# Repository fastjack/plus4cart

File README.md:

# plus4cart
This is an even more modernized (SMD-only) version of the C264Cart.

I removed the through-hole jumpers and other through-hole components and replaced them with SMD versions. Only the (E)EPROM remains as a trough-hole component.

The dimensions of the PCB remain unchanged and it should still fit into the [original looking cartridge case](https://www.thingiverse.com/thing:3657002).

Original README below

# C264Cart

The C264Cart ist a modernized ROM cartridge for the Commodore 264 family of 8-bit computers, the Commodore C16, C116, and Plus/4.

I started out by first reverse engineering and replicating the layout of an original ROM cartridge. Then I adapted it to better suit EPROMS and EEPROMS that are still readily  available today, such as the W27C512 and W27C020.  The layout was also scaled down to save shipping costs, but still fits the original cartridge shells.

See my [blog post](https://www.hackup.net/2023/12/making-cartridges-for-the-commodore-c16-c116-and-plus-4/) for more details.

I also created a simplified version of the original cartridge case for 3D printing that works well with the C264Cart. It is currently available for personal use on [Thingiverse](https://www.thingiverse.com/thing:6309306) and [Printables](https://www.printables.com/model/644139-commodore-264-cartridge-case-redux-for-c16-and-plu).

## Configuration Options

There are two things that need to be configured, the type of EPROM to be used and the size of the targeted ROM images. 

The C264Cart can be configured to support either 16k ROM images or 32k ROM images by setting JP6 and JP7 accordingly. 32k ROM images for the 264 computers usually consist of two 16k parts that were originally stored in two separate ROMs. On the C264Cart in 32k mode, both parts go into the same EPROM with the upper part directly following the lower one. As a result, A14 cannot be used for external bank switching in 32k mode. It is automatically selected by the cartridge.

If the C264Cart is configured for 16k mode R1, D1, and D2 don't need to be populated. These components are used in 32k mode, only.

The C264Cart supports 27C512, 27C020, and 27C040 (E)EPROMs. Make sure that these ICs are always aligned to the top of the cartridge as indicated on the silkscreen and that the jumpers JP4 and JP5 are set correctly!

### 27C512 for 4 ROM images with 16k each

| Address   |             | A14 | A15 |
|----------:|-------------|:---:|:---:|
| 0x0000    | ROM 1       |  0  |  0  |
| 0x4000    | ROM 2       |  1  |  0  |
| 0x8000    | ROM 3       |  0  |  1  |
| 0xC000    | ROM 4       |  1  |  1  |

### 27C020 for 16 ROM images with 16k each

| Address    |             | A14 | A15 | A16 | A17 |
|-----------:|-------------|:---:|:---:|:---:|:---:|
| 0x00000    | ROM 1       |  0  |  0  |  0  |  0  |
| 0x04000    | ROM 2       |  1  |  0  |  0  |  0  |
| 0x08000    | ROM 3       |  0  |  1  |  0  |  0  |
| 0x0C000    | ROM 4       |  1  |  1  |  0  |  0  |
| 0x10000    | ROM 5       |  0  |  0  |  1  |  0  |
| ...        | ...         | ... | ... | ... | ... |
| 0x3C000    | ROM 16      |  1  |  1  |  1  |  1  |

### 27C040 for 32 ROM images with 16k each

| Address    |             | A14 | A15 | A16 | A17 | A18 |
|-----------:|-------------|:---:|:---:|:---:|:---:|:---:|
| 0x00000    | ROM 1       |  0  |  0  |  0  |  0  |  0  |
| 0x04000    | ROM 2       |  1  |  0  |  0  |  0  |  0  |
| 0x08000    | ROM 3       |  0  |  1  |  0  |  0  |  0  |
| 0x0C000    | ROM 4       |  1  |  1  |  0  |  0  |  0  |
| 0x10000    | ROM 5       |  0  |  0  |  1  |  0  |  0  |
| ...        | ...         | ... | ... | ... | ... | ... |
| 0x7C000    | ROM 32      |  1  |  1  |  1  |  1  |  1  |

### 27C512 for 2 ROM images with 32k each
A14 must be left open!

| Address   |             | A14 | A15 |
|----------:|-------------|:---:|:---:|
| 0x0000    | ROM 1 low   |  x  |  0  |
| 0x4000    | ROM 1 high  |  x  |     |
| 0x8000    | ROM 2 low   |  x  |  1  |
| 0xC000    | ROM 2 high  |  x  |     |

### 27C020 for 8 ROM images with 32k each
A14 must be left open!

| Address    |             | A14 | A15 | A16 | A17 |
|-----------:|-------------|:---:|:---:|:---:|:---:|
| 0x00000    | ROM 1 low   |  x  |  0  |  0  |  0  |
| 0x04000    | ROM 1 high  |  x  |     |     |     |
| 0x08000    | ROM 2 low   |  x  |  1  |  0  |  0  |
| 0x0C000    | ROM 2 high  |  x  |     |     |     |
| ...        | ...         |  x  | ... | ... | ... |
| 0x38000    | ROM 8 low   |  x  |  1  |  1  |  1  |
| 0x3C000    | ROM 8 high  |  x  |     |     |     |

### 27C040 for 16 ROM images with 32k each
A14 must be left open!

| Address    |             | A14 | A15 | A16 | A17 | A18 |
|-----------:|-------------|:---:|:---:|:---:|:---:|:---:|
| 0x00000    | ROM 1 low   |  x  |  0  |  0  |  0  |  0  |
| 0x04000    | ROM 1 high  |  x  |     |     |     |     |
| 0x08000    | ROM 2 low   |  x  |  1  |  0  |  0  |  0  |
| 0x0C000    | ROM 2 high  |  x  |     |     |     |     |
| ...        | ...         |  x  | ... | ... | ... | ... |
| 0x78000    | ROM 16 low  |  x  |  1  |  1  |  1  |  1  |
| 0x7C000    | ROM 16 high |  x  |     |     |     |     |

### Caption

## License

 **USE AT YOUR OWN RISK!**.

[
](http://creativecommons.org/licenses/by-nc-sa/4.0/)

This work is licensed under a
[Creative Commons Attribution-NonCommercial-ShareAlike 4.0 International License](http://creativecommons.org/licenses/by-nc-sa/4.0/).

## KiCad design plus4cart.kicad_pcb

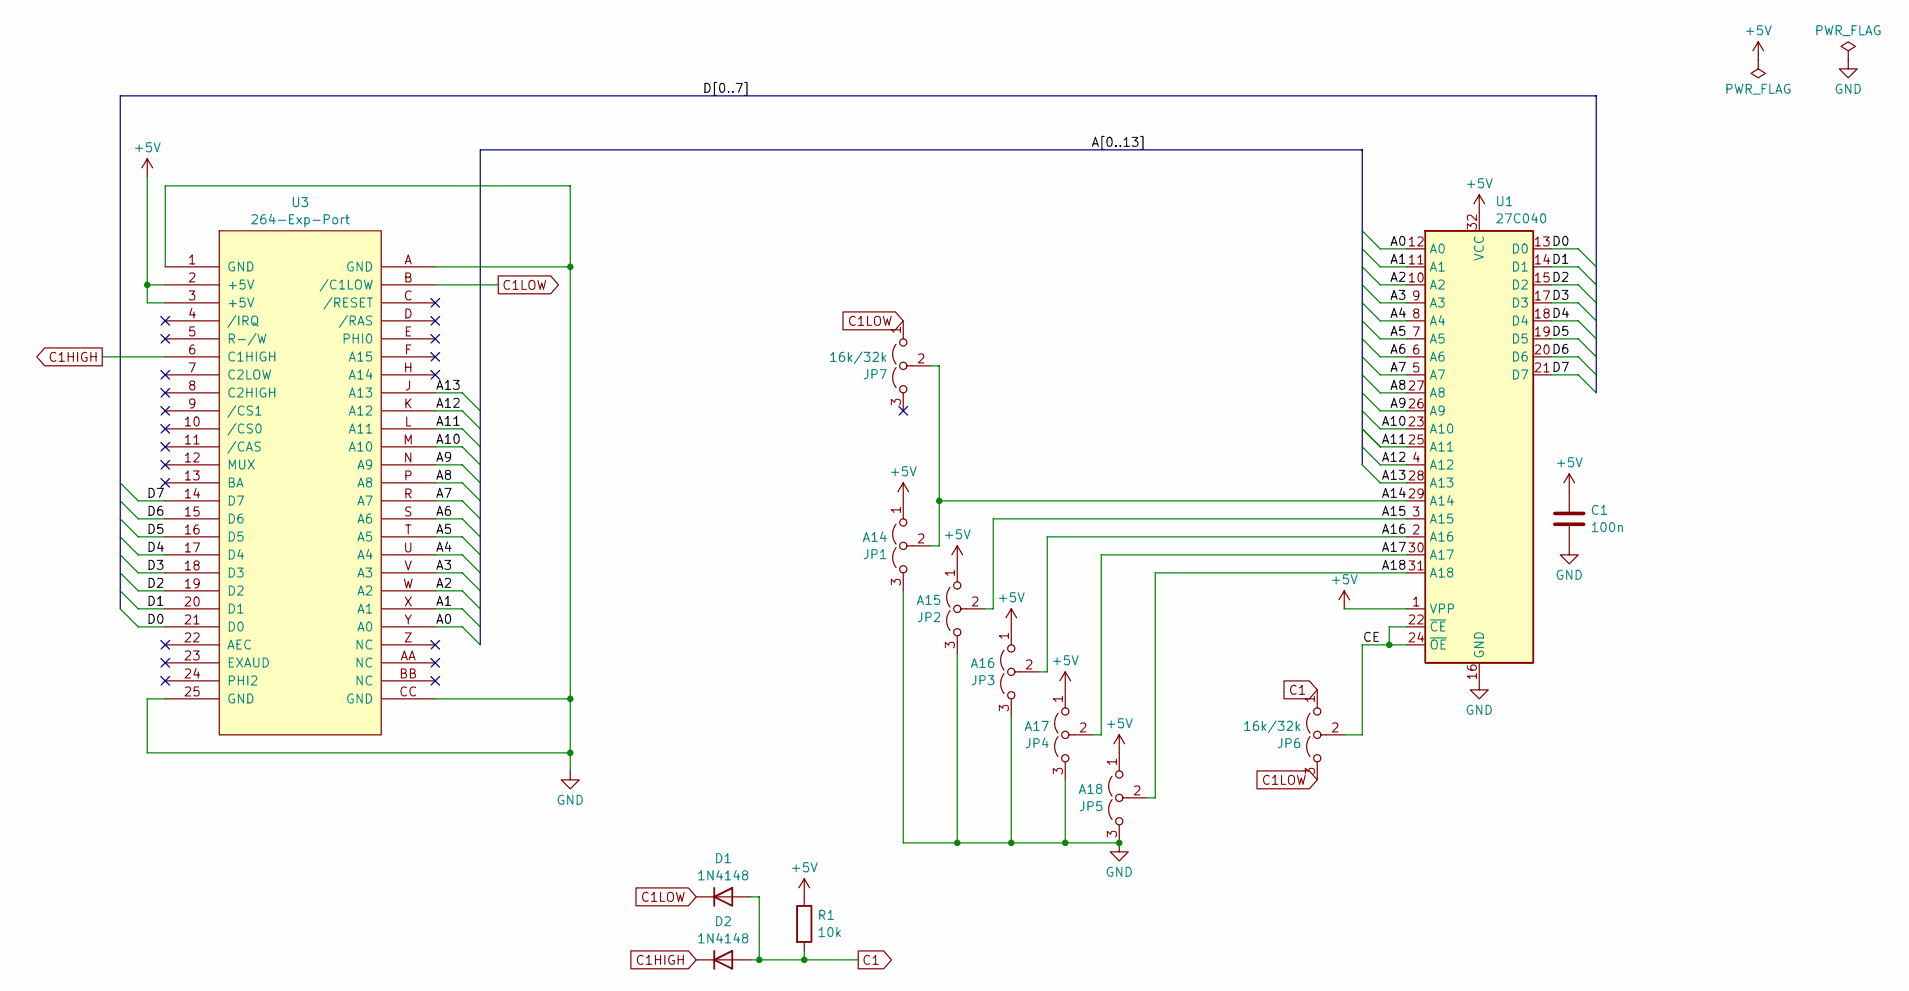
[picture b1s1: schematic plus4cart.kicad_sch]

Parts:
C1: 100n; C_0603_1608Metric
D1, D2: 1N4148; D_SOD-323
JP1: A14; SolderJumper-3_P1.3mm_Open_RoundedPad1.0x1.5mm
JP2: A15; SolderJumper-3_P1.3mm_Open_RoundedPad1.0x1.5mm
JP3: A16; SolderJumper-3_P1.3mm_Open_RoundedPad1.0x1.5mm
JP4: A17; SolderJumper-3_P1.3mm_Open_RoundedPad1.0x1.5mm
JP5: A18; SolderJumper-3_P1.3mm_Open_RoundedPad1.0x1.5mm
JP6: 16k/32k; SolderJumper-3_P1.3mm_Open_RoundedPad1.0x1.5mm
JP7: 16k/32k; SolderJumper-2_P1.3mm_Open_RoundedPad1.0x1.5mm
R1: 10k; R_0603_1608Metric
U1: 27C040; DIP-28-32_W15.24mm
U3: 264-Exp-Port; C264-Cart-NoSilkS

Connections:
+5V: C1.1, JP1.1 (A), JP2.1 (A), JP3.1 (A), JP4.1 (A), JP5.1 (A), R1.1, U1.1 (VPP), U1.32 (VCC), U3.2 (+5V), U3.3 (+5V)
/A0: U1.12 (A0), U3.Y (A0)
/A1: U1.11 (A1), U3.X (A1)
/A2: U1.10 (A2), U3.W (A2)
/A3: U1.9 (A3), U3.V (A3)
/A4: U1.8 (A4), U3.U (A4)
/A5: U1.7 (A5), U3.T (A5)
/A6: U1.6 (A6), U3.S (A6)
/A7: U1.5 (A7), U3.R (A7)
/A8: U1.27 (A8), U3.P (A8)
/A9: U1.26 (A9), U3.N (A9)
/A10: U1.23 (A10), U3.M (A10)
/A11: U1.25 (A11), U3.L (A11)
/A12: U1.4 (A12), U3.K (A12)
/A13: U1.28 (A13), U3.J (A13)
/A14: JP1.2 (C), JP7.2 (C), U1.29 (A14)
/A15: JP2.2 (C), U1.3 (A15)
/A16: JP3.2 (C), U1.2 (A16)
/A17: JP4.2 (C), U1.30 (A17)
/A18: JP5.2 (C), U1.31 (A18)
/CE: JP6.2 (C), U1.22 (~CE), U1.24 (~OE)
/D0: U1.13 (D0), U3.21 (D0)
/D1: U1.14 (D1), U3.20 (D1)
/D2: U1.15 (D2), U3.19 (D2)
/D3: U1.17 (D3), U3.18 (D3)
/D4: U1.18 (D4), U3.17 (D4)
/D5: U1.19 (D5), U3.16 (D5)
/D6: U1.20 (D6), U3.15 (D6)
/D7: U1.21 (D7), U3.14 (D7)
C1: D1.2 (A), D2.2 (A), JP6.1 (A), R1.2
C1HIGH: D2.1 (K), U3.6 (C1HIGH)
C1LOW: D1.1 (K), JP6.3 (B), JP7.1 (A), U3.B (/C1LOW)
GND: C1.2, JP1.3 (B), JP2.3 (B), JP3.3 (B), JP4.3 (B), JP5.3 (B), U1.16 (GND), U3.1 (GND), U3.25 (GND), U3.A (GND), U3.CC (GND)

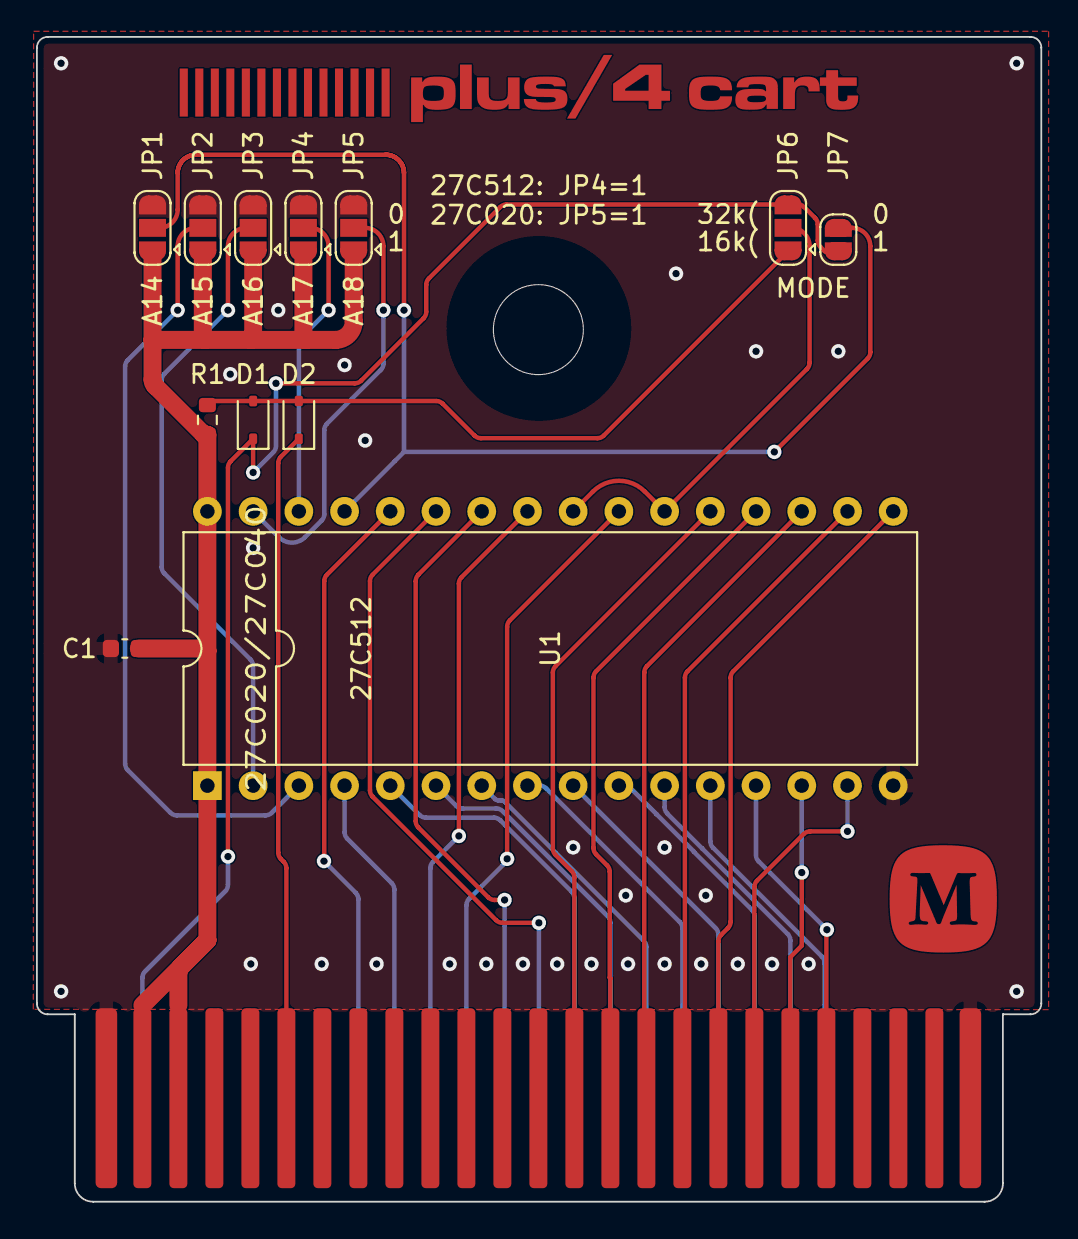
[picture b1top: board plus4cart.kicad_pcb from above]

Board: 2 copper layers, 55.8 x 64.7 mm, 13 parts (0 on the bottom side), 33 nets.

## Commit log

2026-05-03 updated to SMD components (except EPROM)
2026-05-03 renamed project
2026-05-03 updated pdf schematic
2026-05-03 updated schema/pcb metadata
